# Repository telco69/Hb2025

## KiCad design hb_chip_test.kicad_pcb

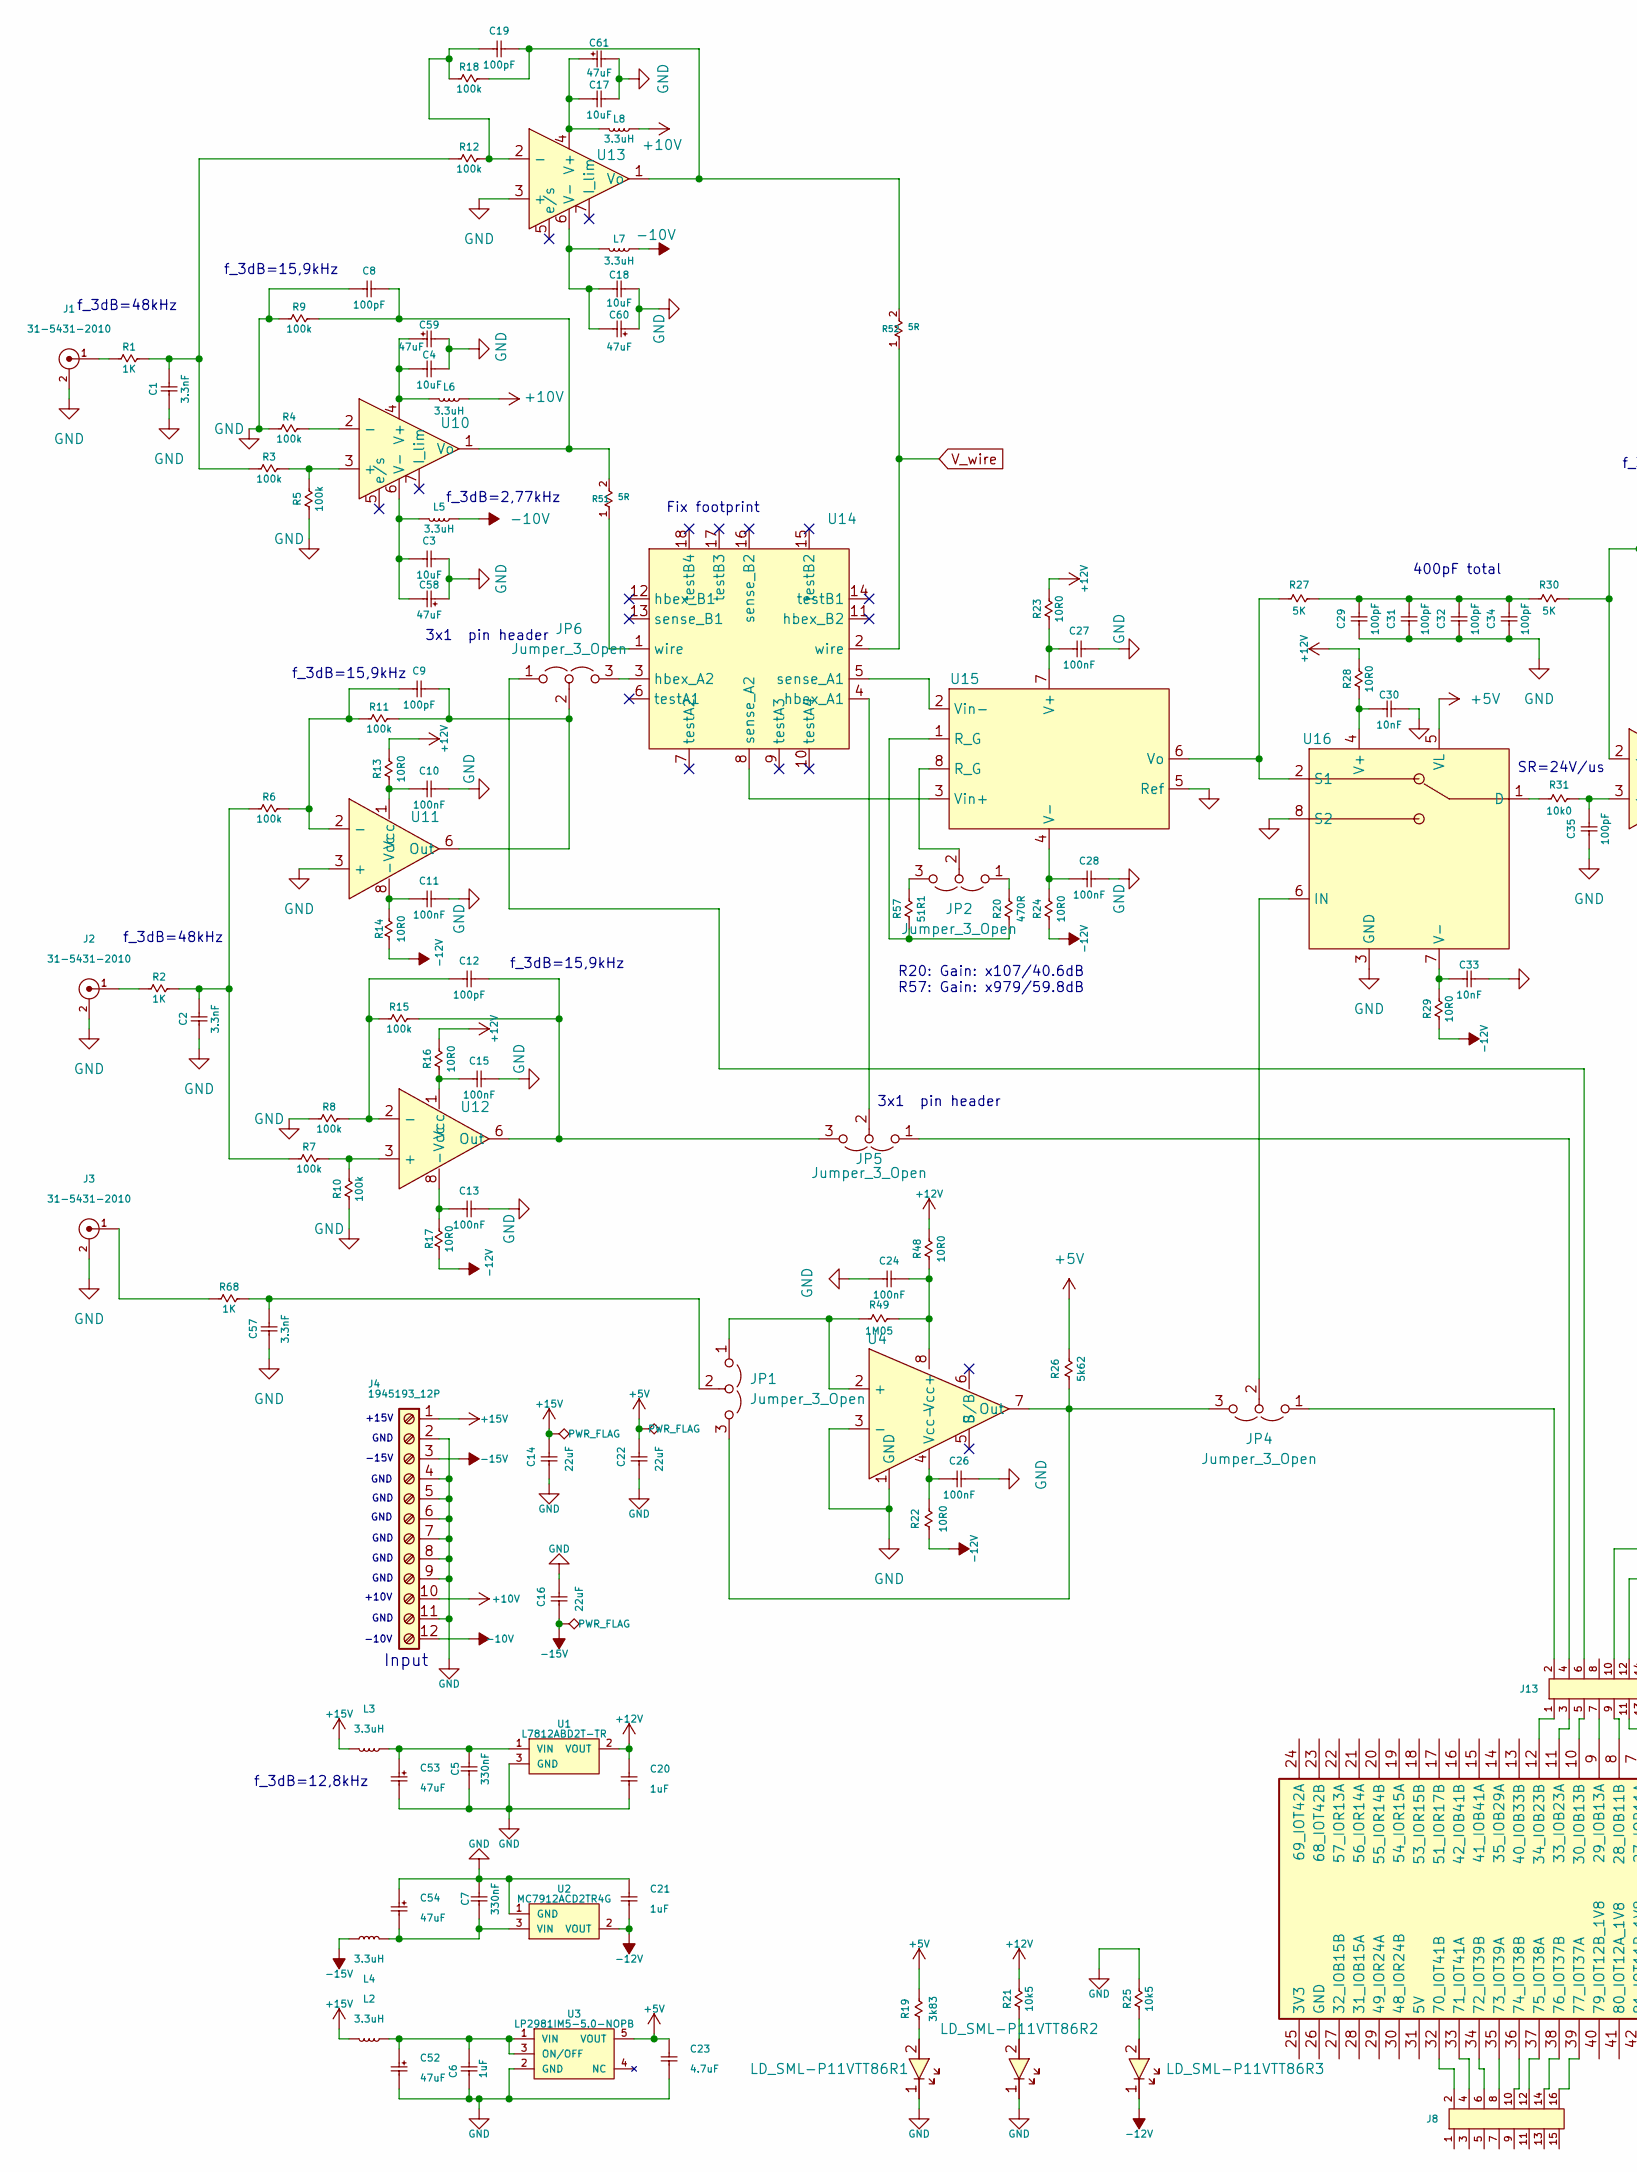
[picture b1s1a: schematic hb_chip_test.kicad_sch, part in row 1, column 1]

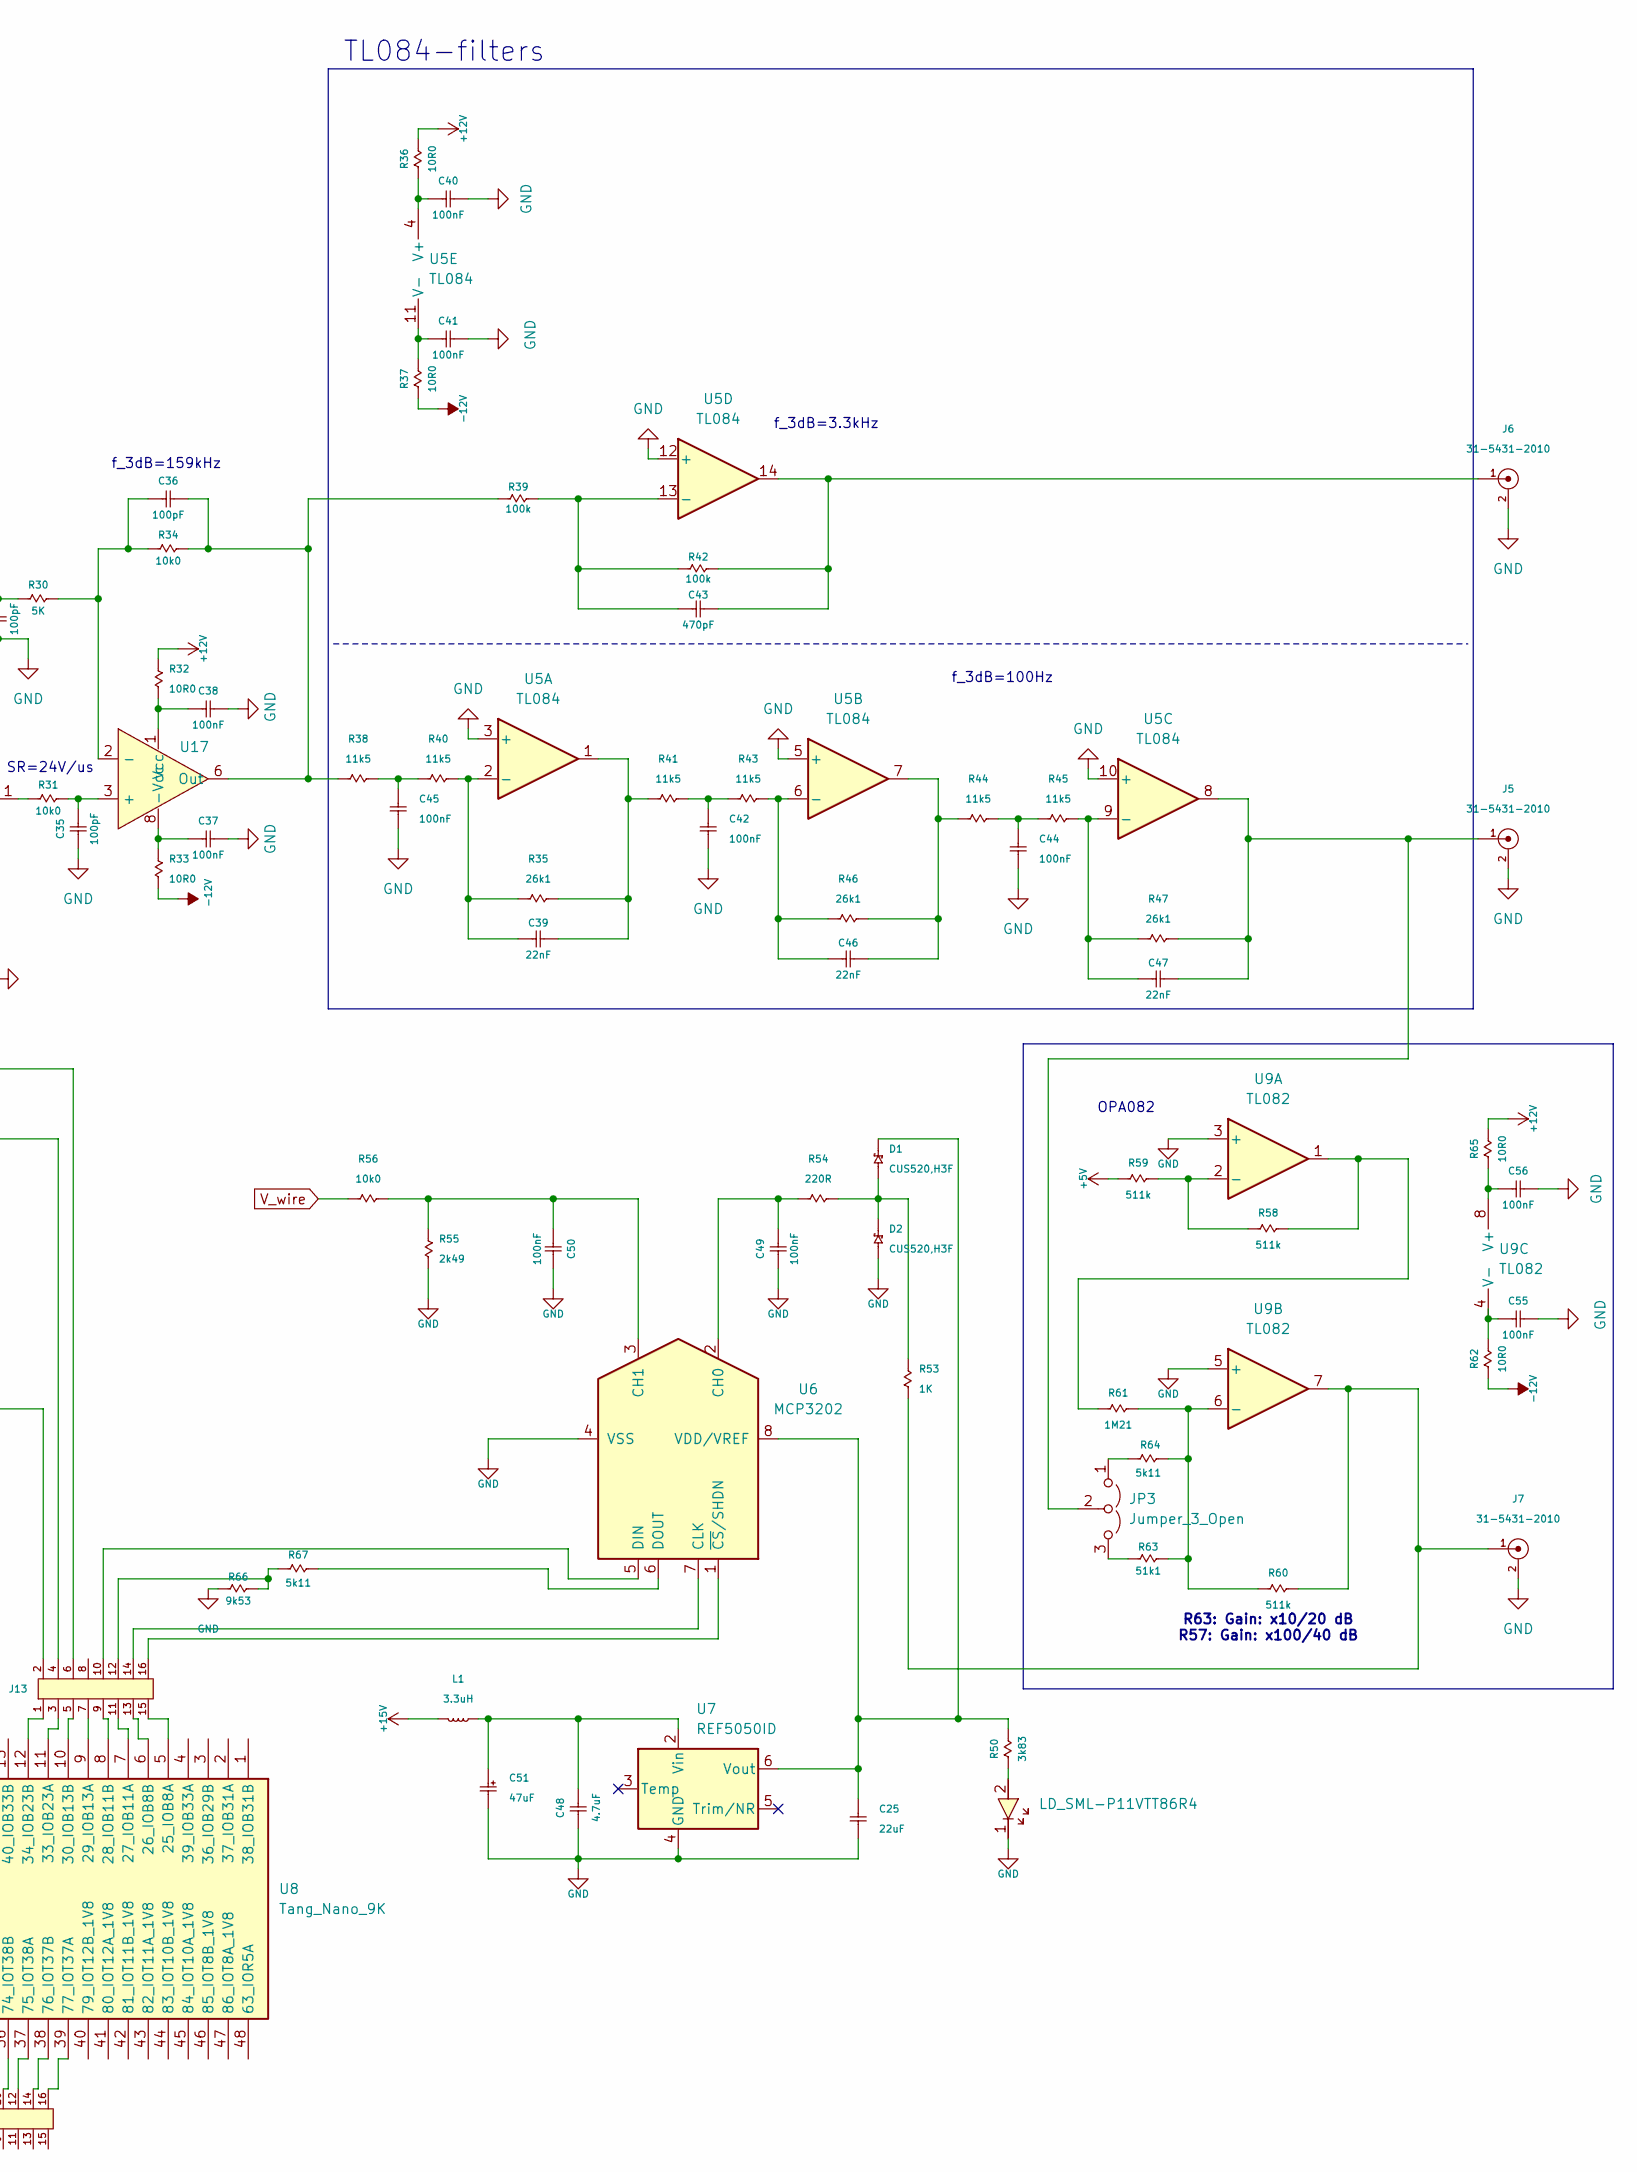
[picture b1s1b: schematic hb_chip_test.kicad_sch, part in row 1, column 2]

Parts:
C1, C2, C57: C_0402_3.3nF_16V_X7R_CID1.2.2599; C0402_CAPC100X50X61L25N; Tolerance 5.0 %; Voltage 16.0 V; MPN 0402YC332JAT2A
C3, C4, C17, C18: C_2220_10uF_50V_X7R_CID1.2.4299; C2220_CAPC570X500X270L60N; Tolerance 5.0 %; Voltage 50.0 V; MPN 22205C106JAT2A
C5, C7: C_0805_330nF_50V_X7R_CID1.2.632; C0805_CAPC200X125X130L45N; MPN CL21B334KBFNNNE
C6, C20, C21: C_0805_1uF_16V_X7R_CID1.2.3095; C0805_CAPC200X125X130L45N; Tolerance 5.0 %; Voltage 16.0 V; MPN 0805YC105JAT2A
C8, C9, C12, C19, C29, C31, C32, C34, C35, C36: C_0402_100pF_50V_C0G_CID1.2.681; C0402_CAPC100X50X61L25N; Tolerance 5.0 %; Voltage 50.0 V; MPN 04025A101JAT2A
C10, C11, C13, C15, C24, C26, C27, C28, C37, C38, C40, C41, C42, C44, C45, C49, C50, C55, C56: C_0805_100nF_16V_X7R_CID1.2.3078; C0805_CAPC200X125X130L45N; Tolerance 5.0 %; Voltage 16.0 V; MPN 0805YC104JAT2A
C14, C16, C22, C25: C_2220_22uF_25V_X7R_CID1.2.4254; C2220_CAPC570X500X270L60N; Tolerance 5.0 %; Voltage 25.0 V; MPN 22203C226JAT2A
C23, C48: C_1812_4.7uF_25V_X7R_CID1.2.4026; C1812_CAPC450X320X280L60N; Tolerance 5.0 %; Voltage 25.0 V; MPN 18123C475JAT2A
C30, C33: C_0402_10nF_16V_X7R_CID1.2.2607; C0402_CAPC100X50X61L25N; Tolerance 5.0 %; Voltage 16.0 V; MPN 0402YC103JAT2A
C39, C46, C47: C_0402_22nF_16V_X7R_CID1.2.2613; C0402_CAPC100X50X61L25N; Tolerance 5.0 %; Voltage 16.0 V; MPN 0402YC223JAT2A
C43: C_0402_470pF_50V_C0G_CID1.2.184; C0402_CAPC100X50X61L25N; Capacitance Tolerance ±5%; Voltage Rating (DC) 50.0 V; MPN GCM1555C1H471JA16D
C51, C52, C53, C54, C58, C59, C60, C61: C_2917_47uF_20V_20%_CID1.3.892; C2917_CAPC730X430X310L130N; MPN 20TQC47MYFT
D1, D2: CUS520,H3F_CID4.2.447; SOD250X130X120L30X30N; MPN CUS520,H3F
J1, J2, J3, J5, J6, J7: 31-5431-2010_CID2.5.196; AMPHENOL_31-5431-2010; MPN 31-5431-2010
J4: 1945193_12P_CID2.2.928; PHOENIX_1945193_12P; MPN 1945193_12P
J8, J13: 2x8; HEADER-P254-2x8
JP1, JP2, JP3, JP4, JP5, JP6: Jumper_3_Open; HEADER-P254-1x3
L1, L2, L3, L4, L5, L6, L7, L8: L_3.3uH_870mA_CID7.3.944; L0805_INDC200X125X140L50N; MPN BRC2012T3R3MD
LD_SML-P11VTT86R1, LD_SML-P11VTT86R2, LD_SML-P11VTT86R3, LD_SML-P11VTT86R4: SML_P11; MPN SML-P11VTT86R
R1, R2, R53, R68: R_0805_1K_CID10.99.611; R0805_RESC200X125X50L35N; MPN Y16291K00000B9R
R3, R4, R5, R6, R7, R8, R9, R10, R11, R12, R15, R18, R39, R42: R_0805_100k_CID10.9.5903; R0805_RESC200X125X50L35N; Tolerance 1.0 %; Voltage 50.0 V; MPN CRCW0805100KFKEA
R13, R14, R16, R17, R22, R23, R24, R28, R29, R32, R33, R36, R37, R48, R62, R65: R_0805_10R0_CID10.9.4757; R0805_RESC200X125X50L35N; Tolerance 1.0 %; Voltage 50.0 V; MPN 40010260210R0F4
R19, R50: R_0805_3k83_CID10.9.461; R0805_RESC200X125X50L35N; Power Rating 125.0 mW; Resistance Tolerance ±1%; MPN CRCW08053K83FKEA
R20: R_0402_470R_CID10.9.70; R0402_RESC100X50X37L20N; Power Rating 100.0 mW; Resistance Tolerance ±1%; MPN ERJ-2RKF4700X
R21, R25: R_0805_10k5_CID10.9.5868; R0805_RESC200X125X50L35N; Tolerance 1.0 %; Voltage 50.0 V; MPN CRCW080510K5FKEA
R26: R_0805_5k62_CID10.9.159; R0805_RESC200X125X50L35N; Power Rating 125.0 mW; Resistance Tolerance ±1%; MPN CRCW08055K62FKEA
R27, R30: R_0805_5K_CID10.99.612; R0805_RESC200X125X50L35N; MPN Y16295K00000T9R
R31, R34, R56: R_0805_10k0_CID10.9.476; R0805_RESC200X125X50L35N; Power Rating 125.0 mW; Resistance Tolerance ±1%; MPN CRCW080510K0FKEA
R35, R46, R47: R_0805_26k1_CID10.9.5881; R0805_RESC200X125X50L35N; Tolerance 1.0 %; Voltage 50.0 V; MPN CRCW080526K1FKEA
R38, R40, R41, R43, R44, R45: R_0805_11k5_CID10.9.5870; R0805_RESC200X125X50L35N; Tolerance 1.0 %; Voltage 50.0 V; MPN CRCW080511K5FKEA
R49: R_0805_1M05_CID10.9.5947; R0805_RESC200X125X50L35N; Tolerance 1.0 %; Voltage 50.0 V; MPN CRCW08051M05FKEA
R51, R52: 5R; TO-220-2_Horizontal_TabDown; MPN PWR220T-35-5R00F
R54: R_0805_220R_CID10.9.602; R0805_RESC200X125X50L35N; Power Rating 125.0 mW; Resistance Tolerance ±1%; MPN CRCW0805220RFKEAHP
R55: R_0805_2k49_CID10.9.5859; R0805_RESC200X125X50L35N; Tolerance 1.0 %; Voltage 50.0 V; MPN CRCW08052K49FKEA
R57: R_0805_51R1_CID10.9.208; R0805_RESC200X125X50L35N; Power Rating 125.0 mW; Resistance Tolerance ±1%; MPN CRCW080551R1FKEA
R58, R59, R60: R_0805_511k_CID10.9.489; R0805_RESC200X125X50L35N; Power Rating 125.0 mW; Resistance Tolerance ±1%; MPN CRCW0805511KFKEA
R61: R_0805_1M21_CID10.9.5950; R0805_RESC200X125X50L35N; Tolerance 1.0 %; Voltage 50.0 V; MPN CRCW08051M21FKEA
R63: R_0805_51k1_CID10.9.5890; R0805_RESC200X125X50L35N; Tolerance 1.0 %; Voltage 50.0 V; MPN CRCW080551K1FKEA
R64, R67: R_0805_5k11_CID10.9.467; R0805_RESC200X125X50L35N; Power Rating 125.0 mW; Resistance Tolerance ±1%; MPN CRCW08055K11FKEA
R66: R_0805_9k53_CID10.9.5867; R0805_RESC200X125X50L35N; Tolerance 1.0 %; Voltage 50.0 V; MPN CRCW08059K53FKEA
U1: L7812ABD2T-TR_CID8.52.934; DPAK3P508_1419X457L172X97T635X1023N; MPN L7812ABD2T-TR
U2: MC7912ACD2TR4G_CID8.52.429; DPAK3P508_1419X457L172X97T635X1023N; MPN MC7912ACD2TR4G
U3: LP2981IM5-5.0-NOPB_CID8.52.176; SOT23-5P95_270X145L35X35N; Current Rating 100.0mA; Dropout Voltage 200.0mV; MPN LP2981IM5-5.0-NOPB
U4: SO-8_3.9x4.9mm_P1.27mm; MPN LM311DT
U5: TL084; SOIC-14_3.9x8.7mm_P1.27mm
U6: MCP3202; SOIC-8_3.9x4.9mm_P1.27mm
U7: REF5050ID; SOIC-8_3.9x4.9mm_P1.27mm
U8: Tang_Nano_9K; DIP-48_TangNano9K
U9: TL082; SOIC8P127_490X600X175L83X41N
U10, U13: TO-220-7_P2.54x3.8mm_StaggerOdd_Lead5.85mm_TabDown
U11, U12, U16, U17: SOIC-8_3.9x4.9mm_P1.27mm
U14: (no value)
U15: SMDIP-8_W9.53mm

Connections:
+5V: C22.2, C23.1, R19.2, R26.2, R59.1, U3.5 (VOUT), U16.5 (VL)
+10V: J4.10, L6.2, L8.2
+12V: C20.1, R13.2, R16.2, R21.2, R23.2, R28.2, R32.1, R36.2, R48.2, R65.2, U1.2 (VOUT)
+15V: C14.2, J4.1, L1.1, L2.1, L3.1
-10V: J4.12, L5.2, L7.2
-12V: C21.2, LD_SML-P11VTT86R3.1, R14.1, R17.1, R22.1, R24.1, R29.1, R33.2, R37.1, R62.1, U2.2 (VOUT); also elsewhere on the board
-15V: C16.1, J4.3, L4.1
GND: C1.1, C2.1, C3.2, C4.2, C5.1, C6.2, C7.2, C8.1, C10.2, C11.2, C13.2, C14.1, C15.2, C16.2, C17.2, C18.2, C20.2, C21.1, C22.1, C23.2, C24.1, C25.2, C26.2, C27.2, C28.2, C29.1, C30.2, C31.1, C32.1, C33.2, C34.1, C35.1, C37.2, C38.2, C40.2, C41.2, C42.2, C44.2, C45.2, C48.2, C49.1, C50.1, C51.2, C52.2, C53.2, C54.1, C55.2, C56.2, C57.1, C58.1, C59.2, C60.1, C61.2, D2.A, J1.2, J2.2, J3.2, J4.2, J4.4, J4.5, J4.6, J4.7, J4.8, J4.9, J4.11, J5.2, J6.2, J7.2, LD_SML-P11VTT86R1.1, LD_SML-P11VTT86R2.1, LD_SML-P11VTT86R4.1, R4.1, R5.1, R8.1, R9.1, R10.1, R25.2, R55.2, R66.1, U1.3 (GND), U2.1 (GND), U3.2 (GND), U4.1 (GND), U4.3 (-), U5.3 (+), U5.5 (+), U5.10 (+), U5.12 (+), U6.4 (VSS), U7.4 (GND), U8.49, U8.50, U9.3 (+), U9.5 (+), U11.3 (+), U13.3 (+), U15.5 (Ref), U16.3 (GND), U16.8 (S2); also elsewhere on the board
unnamed: C1.2, R1.2, R3.1, R12.1
unnamed: C2.2, R2.2, R6.1, R7.1
unnamed: C29.2, C31.2, C32.2, C34.2, R27.2, R30.1
unnamed: C39.2, R35.2, R41.1, U5.1
unnamed: C42.1, R41.2, R43.1
unnamed 13: C43.2, J6.1, R42.2, U5.14; also elsewhere on the board
unnamed: C44.1, R44.2, R45.1
unnamed: C45.1, R38.2, R40.1
unnamed: C46.2, R44.1, R46.2, U5.7
unnamed: D1.A, D2.C, R53.2, R54.2
unnamed 18: J1.1, R1.1; also elsewhere on the board
unnamed 19: J2.1, R2.1; also elsewhere on the board
unnamed 20: J3.1, R68.1; also elsewhere on the board
unnamed 21: J7.1, R53.1, R60.2, U9.7; also elsewhere on the board
unnamed: J13.12, R66.2, R67.1
unnamed: JP1.1 (A), R49.1, U4.2 (+)
unnamed: JP1.3 (B), JP4.3 (B), R26.1, U4.7 (Out)
unnamed: C57.2, JP1.2 (C), R68.2
unnamed: JP2.1 (A), R20.2
unnamed: JP2.3 (B), R57.2
unnamed: JP2.2 (C), U15.8 (R_G)
unnamed: JP3.1 (A), R64.1
unnamed: JP3.3 (B), R63.1
unnamed 31: C47.2, J5.1, JP3.2 (C), R47.2, U5.8; also elsewhere on the board
unnamed: J13.2, JP4.1 (A)
unnamed: JP4.2 (C), U16.6 (IN)
unnamed: J13.4, JP5.1 (A)
unnamed: C12.2, JP5.3 (B), R15.2, U12.6 (Out)
unnamed: JP5.2 (C), U14.4 (hbex_A1)
unnamed: J13.6, JP6.1 (A)
unnamed: JP6.3 (B), U14.3 (hbex_A2)
unnamed: C9.2, JP6.2 (C), R11.2, U11.6 (Out)
unnamed 40: LD_SML-P11VTT86R1.2, R19.1; also elsewhere on the board
unnamed 41: LD_SML-P11VTT86R2.2, R21.1; also elsewhere on the board
unnamed 42: LD_SML-P11VTT86R3.2, R25.1; also elsewhere on the board
unnamed 43: LD_SML-P11VTT86R4.2, R50.1; also elsewhere on the board
unnamed: R20.1, R57.1, U15.1 (R_G)
unnamed: R51.1, U14.1 (wire)
unnamed: R58.2, R61.1, U9.1
unnamed: C5.2, C53.1, L3.2, U1.1 (VIN)
unnamed: C7.1, C54.2, L4.2, U2.3 (VIN)
unnamed: C6.1, C52.1, L2.2, U3.1 (VIN), U3.3 (ON/OFF)
unnamed: C24.2, R48.1, R49.2, U4.8 (Vcc+)
unnamed: C26.1, R22.2, U4.4 (Vcc-)
unnamed: C39.1, R35.1, R40.2, U5.2 (-)
unnamed: C46.1, R43.2, R46.1, U5.6 (-)
unnamed: C47.1, R45.2, R47.1, U5.9 (-)
unnamed: C43.1, R39.2, R42.1, U5.13 (-)
unnamed: C40.1, R36.1, U5.4 (V+)
unnamed: C41.1, R37.2, U5.11 (V-)
unnamed: C49.2, R54.1, U6.2 (CH0)
unnamed: C50.2, R55.1, R56.2, U6.3 (CH1)
unnamed: J13.14, U6.7 (CLK)
unnamed: J13.10, U6.5 (DIN)
unnamed: R67.2, U6.6 (DOUT)
unnamed: C25.1, D1.C, R50.2, U6.8 (VDD/VREF), U7.6 (Vout)
unnamed: J13.16, U6.1 (~CS/SHDN)
unnamed: C48.1, C51.1, L1.2, U7.2 (Vin)
unnamed: J13.15, U8.5 (25_IOB8A)
unnamed: J13.13, U8.6 (26_IOB8B)
unnamed: J13.11, U8.7 (27_IOB11A)
unnamed: J13.9, U8.8 (28_IOB11B)
unnamed: J13.7, U8.9 (29_IOB13A)
unnamed: J13.5, U8.10 (30_IOB13B)
unnamed: J13.3, U8.11 (33_IOB23A)
unnamed: J13.1, U8.12 (34_IOB23B)
unnamed: J8.2, U8.32 (70_IOT41B)
unnamed: J8.4, U8.33 (71_IOT41A)
unnamed: J8.6, U8.34 (72_IOT39B)
unnamed: J8.8, U8.35 (73_IOT39A)
unnamed: J8.10, U8.36 (74_IOT38B)
unnamed: J8.12, U8.37 (75_IOT38A)
unnamed: J8.14, U8.38 (76_IOT37B)
unnamed: J8.16, U8.39 (77_IOT37A)
unnamed: R58.1, R59.2, U9.2 (-)
unnamed: R60.1, R61.2, R63.2, R64.2, U9.6 (-)
unnamed: C56.1, R65.1, U9.8 (V+)
unnamed: C55.1, R62.2, U9.4 (V-)
unnamed: R3.2, R5.2, U10.3 (+)
unnamed: R4.2, U10.2 (-)
unnamed: C4.1, C59.1, L6.1, U10.4 (V+)
unnamed: C3.1, C58.2, L5.1, U10.6 (V-)
unnamed: C8.2, R9.2, R51.2, U10.1 (Vo)
unnamed: C9.1, R6.2, R11.1, U11.2 (-)
unnamed: C11.1, R14.2, U11.8 (-Vcc)
unnamed: C10.1, R13.1, U11.1 (Vcc)
unnamed: R7.2, R10.2, U12.3 (+)
unnamed: C12.1, R8.2, R15.1, U12.2 (-)
unnamed: C13.1, R17.2, U12.8 (-Vcc)
unnamed: C15.1, R16.1, U12.1 (Vcc)
unnamed: C19.1, R12.2, R18.1, U13.2 (-)
unnamed: C17.1, C61.1, L8.1, U13.4 (V+)
unnamed: C18.1, C60.2, L7.1, U13.6 (V-)
unnamed: C19.2, R18.2, R52.2, U13.1 (Vo)
unnamed: U14.5 (sense_A1), U15.2 (Vin-)
unnamed: U14.8 (sense_A2), U15.3 (Vin+)
unnamed: C27.1, R23.1, U15.7 (V+)
unnamed: C28.1, R24.2, U15.4 (V-)
unnamed: R27.1, U15.6 (Vo), U16.2 (S1)
unnamed: R31.1, U16.1 (D)
unnamed: C30.1, R28.1, U16.4 (V+)
unnamed: C33.1, R29.2, U16.7 (V-)
unnamed: C35.2, R31.2, U17.3 (+)
unnamed: C36.1, R30.2, R34.1, U17.2 (-)
unnamed: C37.1, R33.1, U17.8 (-Vcc)
unnamed: C36.2, R34.2, R38.1, R39.1, U17.6 (Out)
unnamed: C38.1, R32.2, U17.1 (Vcc)
V_wire: R52.1, R56.1, U14.2 (wire)

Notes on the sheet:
3x1 pin header
SR=24V/us
f_3dB=48kHz
Input
GND
+15V
Fix footprint
-15V
f_3dB=100Hz
OPA082
f_3dB=159kHz
-10V
f_3dB=15,9kHz
TL084-filters
+10V
f_3dB=3.3kHz
400pF total
R63: Gain: x10/20 dB R57: Gain: x100/40 dB
f_3dB=12,8kHz
R20: Gain: x107/40.6dB R57: Gain: x979/59.8dB
f_3dB=2,77kHz

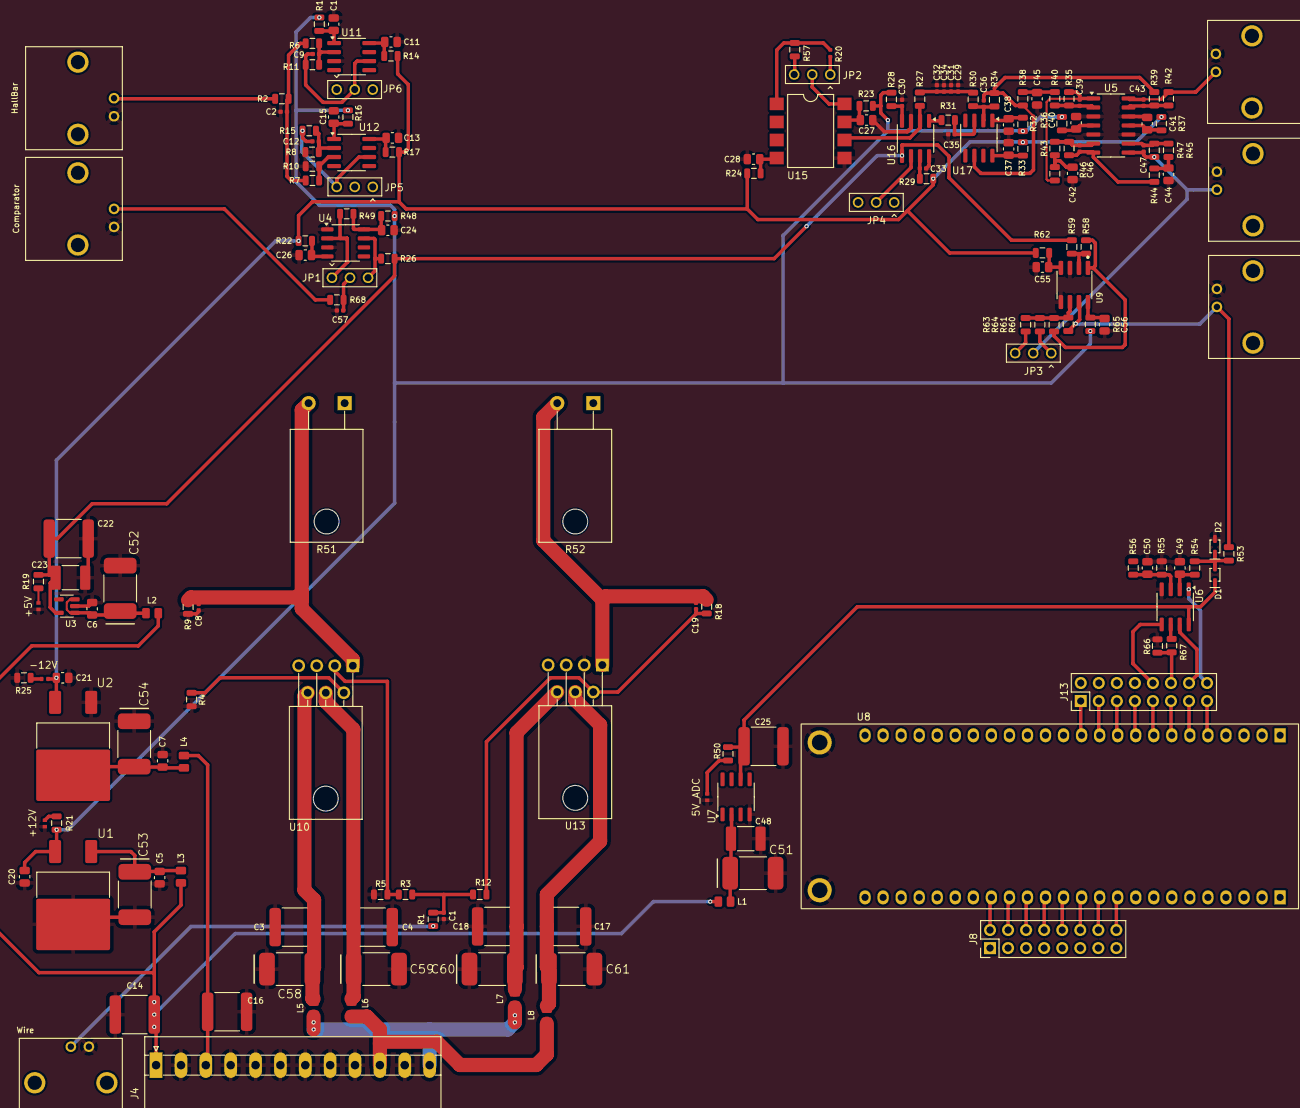
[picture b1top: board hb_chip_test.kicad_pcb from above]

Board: 2 copper layers, 174 parts (0 on the bottom side), 111 nets.

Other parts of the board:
5V_ADC: SML_P11
+5V, +12V: SML_P11
-12V: SML_P11
Comparator: 31-5431-2010_CID2.5.196; AMPHENOL_31-5431-2010
HallBar: 31-5431-2010_CID2.5.196; AMPHENOL_31-5431-2010
NoFilter: 31-5431-2010_CID2.5.196; AMPHENOL_31-5431-2010
Wire: 31-5431-2010_CID2.5.196; AMPHENOL_31-5431-2010
WithFilter: 31-5431-2010_CID2.5.196; AMPHENOL_31-5431-2010
WithGain: 31-5431-2010_CID2.5.196; AMPHENOL_31-5431-2010

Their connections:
-12V: -12V.1; also elsewhere on the board
GND: 5V_ADC.1, +5V.1, +12V.1, Comparator.2, HallBar.2, NoFilter.2, Wire.2, WithFilter.2, WithGain.2; also elsewhere on the board
unnamed 13: NoFilter.1; also elsewhere on the board
unnamed 18: Wire.1; also elsewhere on the board
unnamed 19: HallBar.1; also elsewhere on the board
unnamed 20: Comparator.1; also elsewhere on the board
unnamed 21: WithGain.1; also elsewhere on the board
unnamed 31: WithFilter.1; also elsewhere on the board
unnamed 40: +5V.2; also elsewhere on the board
unnamed 41: +12V.2; also elsewhere on the board
unnamed 42: -12V.2; also elsewhere on the board
unnamed 43: 5V_ADC.2; also elsewhere on the board
